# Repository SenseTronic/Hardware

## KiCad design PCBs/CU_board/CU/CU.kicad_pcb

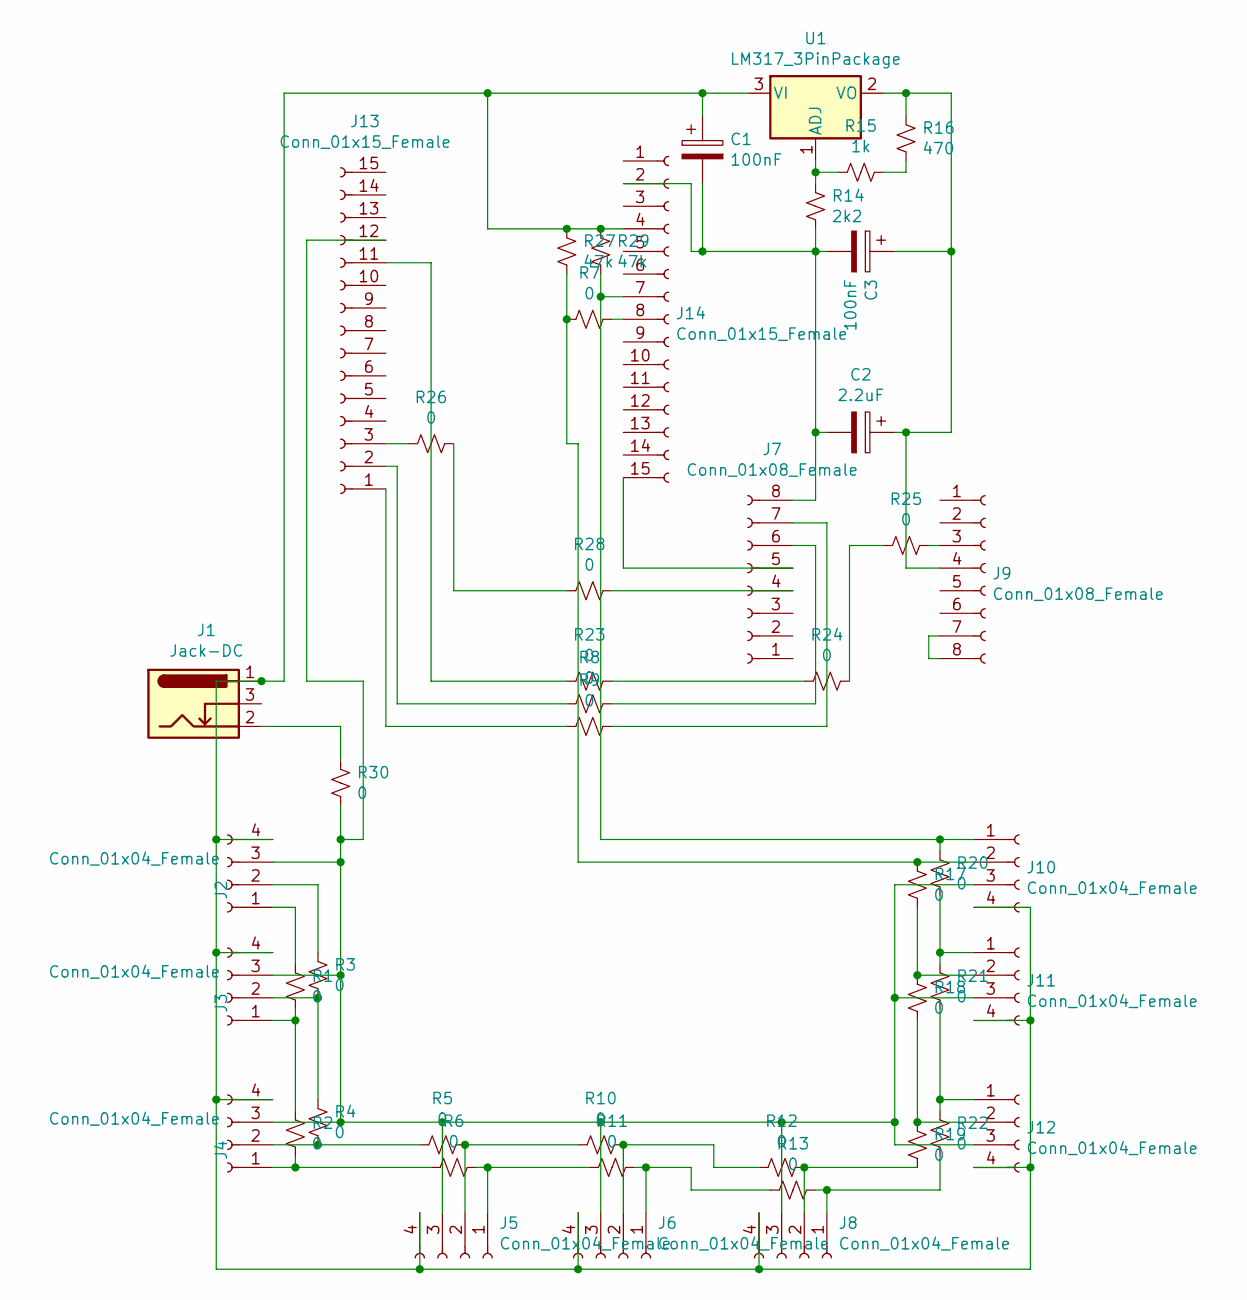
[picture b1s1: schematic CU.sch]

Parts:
C1, C3: 100nF; C_Disc_D4.3mm_W1.9mm_P5.00mm
C2: 2.2uF; CP_Radial_D5.0mm_P2.00mm
J1: Jack-DC; BarrelJack_Horizontal
J2, J3, J4, J5, J6, J8, J10, J11, J12: Conn_01x04_Female; PinSocket_1x04_P2.54mm_Vertical
J7, J9: Conn_01x08_Female; PinSocket_1x08_P2.54mm_Vertical
J13, J14: Conn_01x15_Female; PinSocket_1x15_P2.54mm_Vertical
R1, R2, R3, R4, R5, R6, R7, R8, R9, R10, R11, R12, R13, R17, R18, R19, R20, R21, R22, R23, R24, R25, R26, R28, R30: 0; R_Axial_DIN0207_L6.3mm_D2.5mm_P7.62mm_Horizontal
R14: 2k2; R_Axial_DIN0207_L6.3mm_D2.5mm_P7.62mm_Horizontal
R15: 1k; R_Axial_DIN0207_L6.3mm_D2.5mm_P2.54mm_Vertical
R16: 470; R_Axial_DIN0207_L6.3mm_D2.5mm_P2.54mm_Vertical
R27, R29: 47k; R_Axial_DIN0207_L6.3mm_D2.5mm_P7.62mm_Horizontal
U1: LM317_3PinPackage; TO-220-3_Vertical

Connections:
unnamed: C1.1, J1.1, J2.4, J3.4, J4.4, J5.4, J6.4, J8.4, J10.4, J11.4, J12.4, J14.4, R27.1, R29.1, U1.3 (VI)
unnamed: C1.2, C2.2, C3.2, J7.8, J14.2, R14.1
unnamed: C2.1, C3.1, J9.4, R16.1, U1.2 (VO)
unnamed: J1.2, R30.1
unnamed: J2.1, R1.1
unnamed: J2.2, R3.1
unnamed: J3.1, R1.2, R2.1
unnamed: J3.2, R3.2, R4.1
unnamed: J4.1, R2.2, R6.2
unnamed: J4.2, R4.2, R5.2
unnamed: J5.1, R6.1, R11.2
unnamed: J5.2, R5.1, R10.2
unnamed: J6.1, R11.1, R13.2
unnamed: J6.2, R10.1, R12.2
unnamed: J7.4, R28.1
unnamed: J7.6, R8.1
unnamed: J7.7, R9.1
unnamed: J8.1, R13.1, R22.1
unnamed: J8.2, R12.1, R19.1
unnamed: J9.3, R25.1
unnamed: J9.7, J9.8
unnamed: J10.1, J14.7, R20.2, R29.2
unnamed: J10.2, R7.2, R17.2, R27.2
unnamed: J2.3, J3.3, J4.3, J5.3, J6.3, J8.3, J10.3, J11.3, J12.3, J13.12, R30.2
unnamed: J11.1, R20.1, R21.2
unnamed: J11.2, R17.1, R18.2
unnamed: J12.1, R21.1, R22.2
unnamed: J12.2, R18.1, R19.2
unnamed: J13.1, R9.2
unnamed: J13.2, R8.2
unnamed: J13.3, R26.2
unnamed: J13.11, R23.2
unnamed: J14.8, R7.1
unnamed: J7.5, J14.15
unnamed: R14.2, R15.2, U1.1 (ADJ)
unnamed: R15.1, R16.2
unnamed: R23.1, R24.2
unnamed: R24.1, R25.2
unnamed: R26.1, R28.2

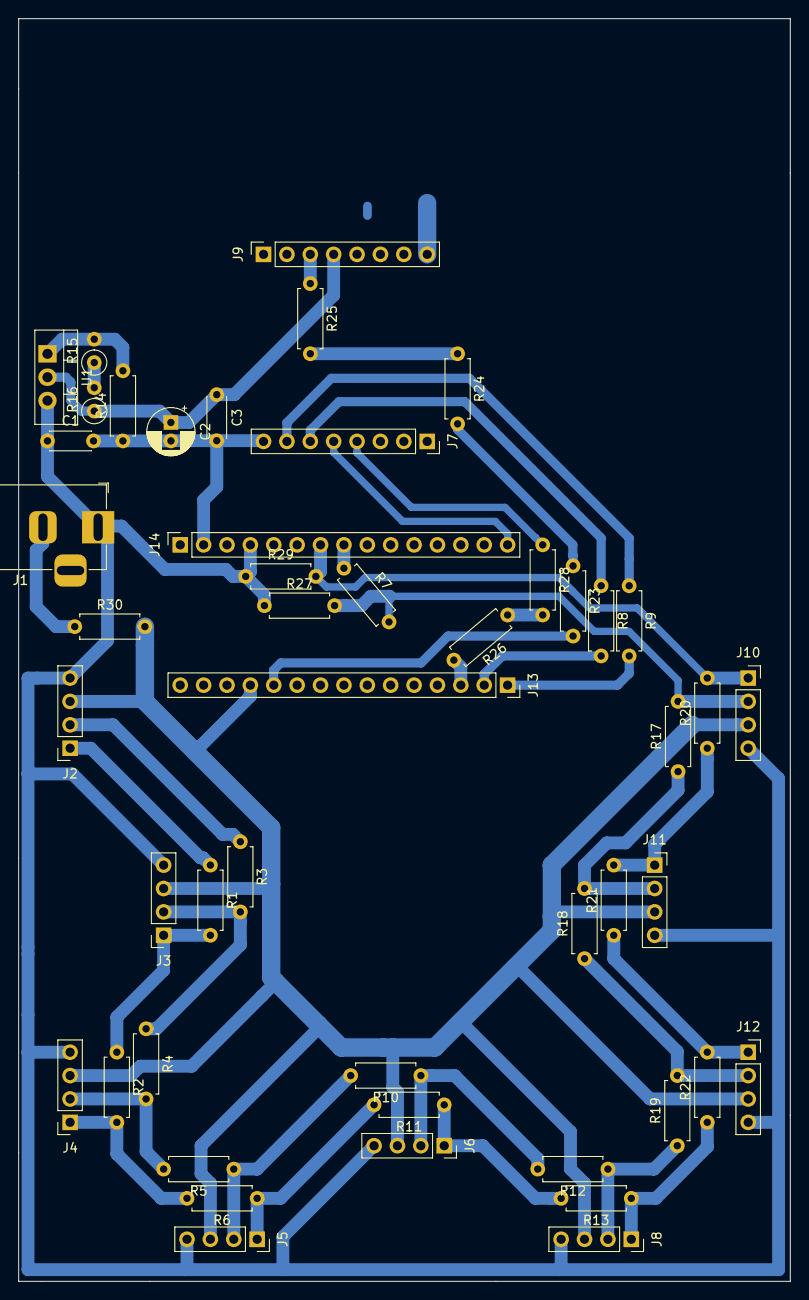
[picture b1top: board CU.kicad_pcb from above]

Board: 2 copper layers, 83.8 x 137.2 mm, 48 parts (0 on the bottom side), 39 nets.

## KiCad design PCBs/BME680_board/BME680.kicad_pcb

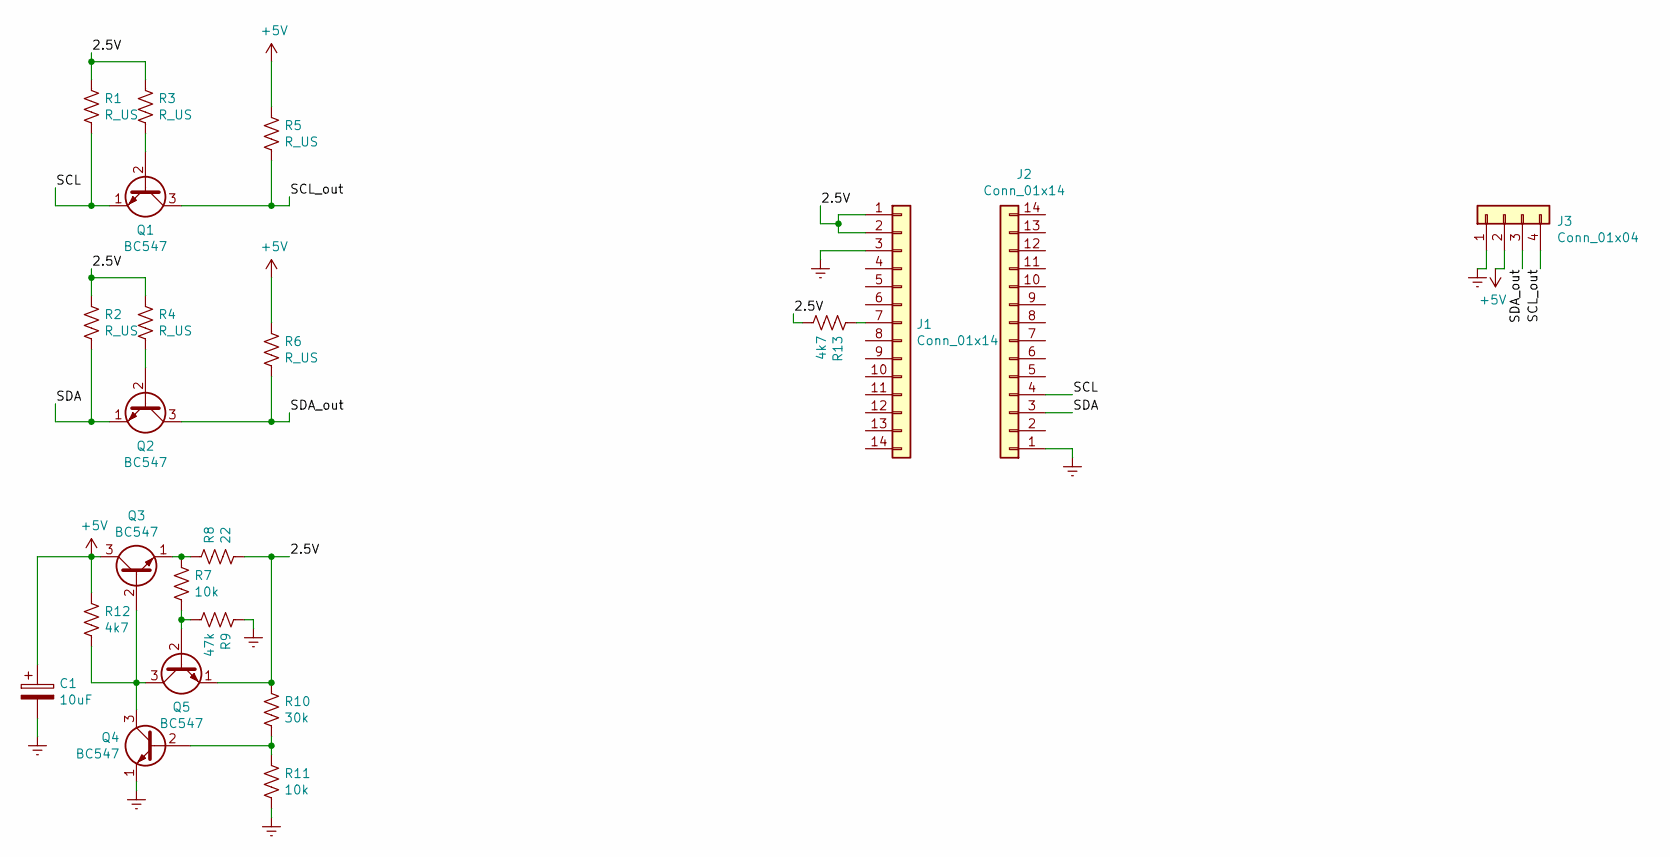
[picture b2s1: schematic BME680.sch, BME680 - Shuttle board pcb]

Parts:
C1: 10uF; CP_Radial_D5.0mm_P2.00mm
J1, J2: Conn_01x14; PinSocket_1x14_P2.54mm_Vertical
J3: Conn_01x04; PinHeader_1x04_P2.54mm_Horizontal
Q1, Q2, Q3, Q4, Q5: BC547; TO-92_Inline
R1, R2, R3, R4, R5, R6: R_US; R_Axial_DIN0207_L6.3mm_D2.5mm_P2.54mm_Vertical
R7, R11: 10k; R_Axial_DIN0207_L6.3mm_D2.5mm_P5.08mm_Vertical
R8: 22; R_Axial_DIN0207_L6.3mm_D2.5mm_P5.08mm_Vertical
R9: 47k; R_Axial_DIN0207_L6.3mm_D2.5mm_P5.08mm_Vertical
R10: 30k; R_Axial_DIN0207_L6.3mm_D2.5mm_P5.08mm_Vertical
R12: 4k7; R_Axial_DIN0207_L6.3mm_D2.5mm_P5.08mm_Vertical
R13: 4k7; R_Axial_DIN0207_L6.3mm_D2.5mm_P7.62mm_Horizontal

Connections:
+5V: C1.1, J3.2, Q3.3 (C), R5.1, R6.1, R12.1
/2.5V: J1.1, J1.2, Q5.1 (E), R1.1, R2.1, R3.1, R4.1, R8.2, R10.1, R13.2
/SCL: J2.4, Q1.1 (E), R1.2
/SCL_out: J3.4, Q1.3 (C), R5.2
/SDA: J2.3, Q2.1 (E), R2.2
/SDA_out: J3.3, Q2.3 (C), R6.2
Earth: C1.2, J1.3, J2.1, J3.1, Q4.1 (E), R9.1, R11.2
unnamed: J1.7, R13.1
unnamed: Q1.2 (B), R3.2
unnamed: Q2.2 (B), R4.2
unnamed: Q3.1 (E), R7.1, R8.1
unnamed: Q3.2 (B), Q4.3 (C), Q5.3 (C), R12.2
unnamed: Q4.2 (B), R10.2, R11.1
unnamed: Q5.2 (B), R7.2, R9.2

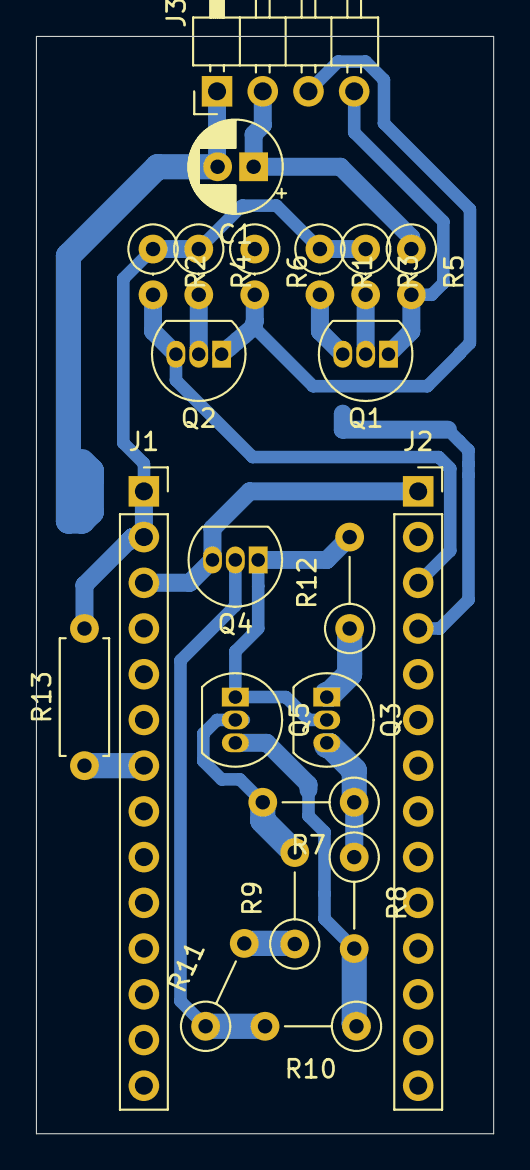
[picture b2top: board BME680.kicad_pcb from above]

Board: 2 copper layers, 25.4 x 61.0 mm, 22 parts (0 on the bottom side), 14 nets.

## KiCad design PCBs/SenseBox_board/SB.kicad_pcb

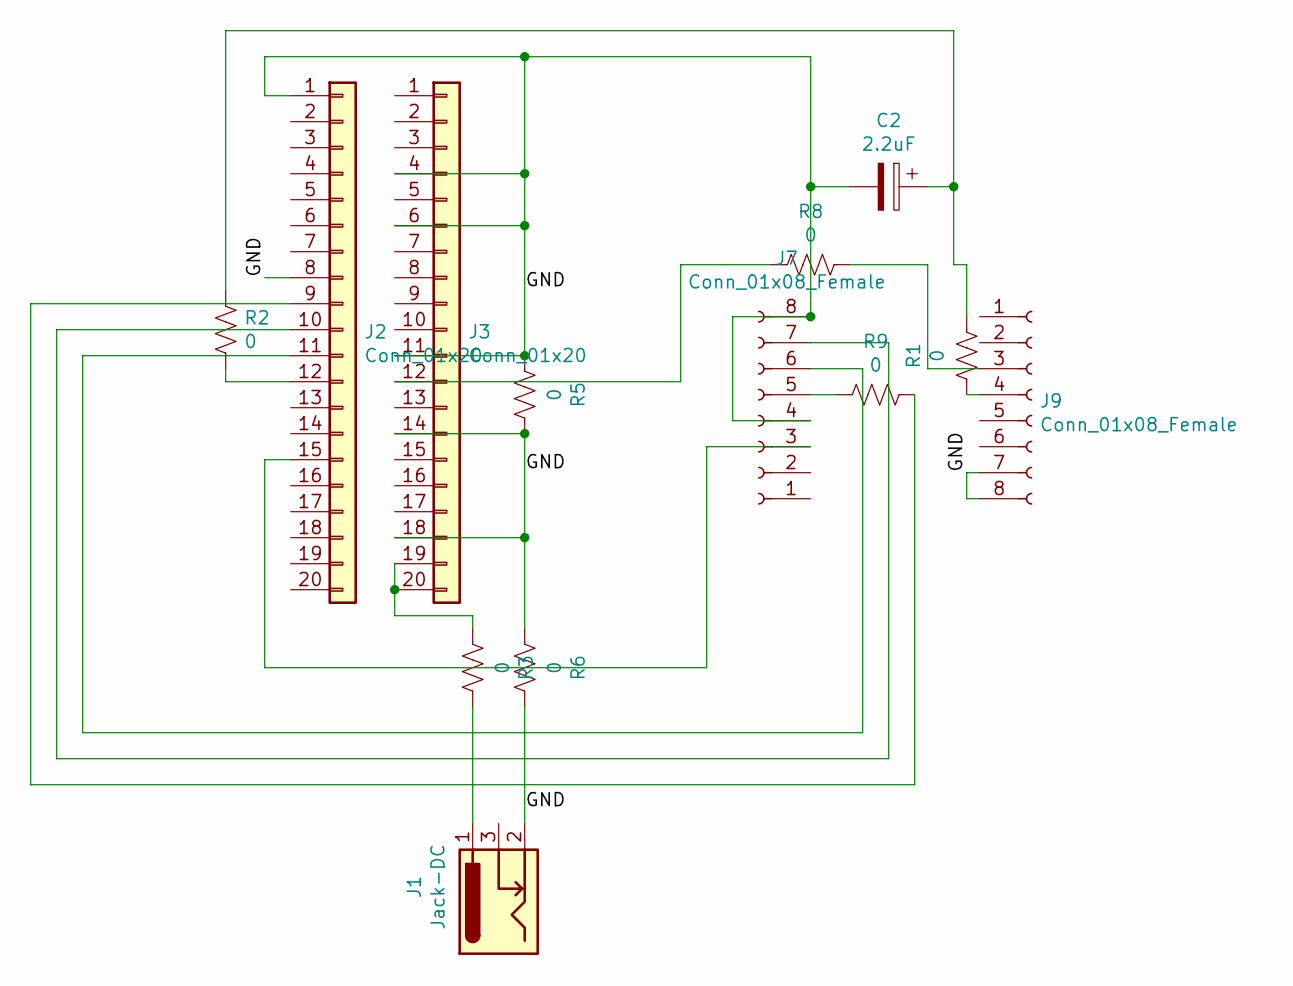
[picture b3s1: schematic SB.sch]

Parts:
C2: 2.2uF; CP_Radial_D5.0mm_P2.00mm
J1: Jack-DC; BarrelJack_Horizontal
J2, J3: Conn_01x20; PinSocket_1x20_P2.54mm_Vertical
J7, J9: Conn_01x08_Female; PinSocket_1x08_P2.54mm_Vertical
R1, R5, R8, R9: 0; R_Axial_DIN0207_L6.3mm_D2.5mm_P7.62mm_Horizontal
R2: 0; R_Axial_DIN0207_L6.3mm_D2.5mm_P15.24mm_Horizontal
R3, R6: 0; R_Axial_DIN0207_L6.3mm_D2.5mm_P10.16mm_Horizontal

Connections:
/GND: C2.2, J1.2, J2.1, J2.8, J3.4, J3.6, J3.11, J3.14, J3.18, J7.4, J7.8, J9.7, J9.8, R5.1, R5.2, R6.1, R6.2
unnamed: C2.1, R1.1, R2.2
unnamed: J1.1, R3.1
unnamed: J2.9, R9.1
unnamed: J2.10, J7.7
unnamed: J2.11, J7.6
unnamed: J2.12, R2.1
unnamed: J2.15, J7.3
unnamed: J3.12, R8.2
unnamed: J3.19, J3.20, R3.2
unnamed: J7.5, R9.2
unnamed: J9.3, R8.1
unnamed: J9.4, R1.2

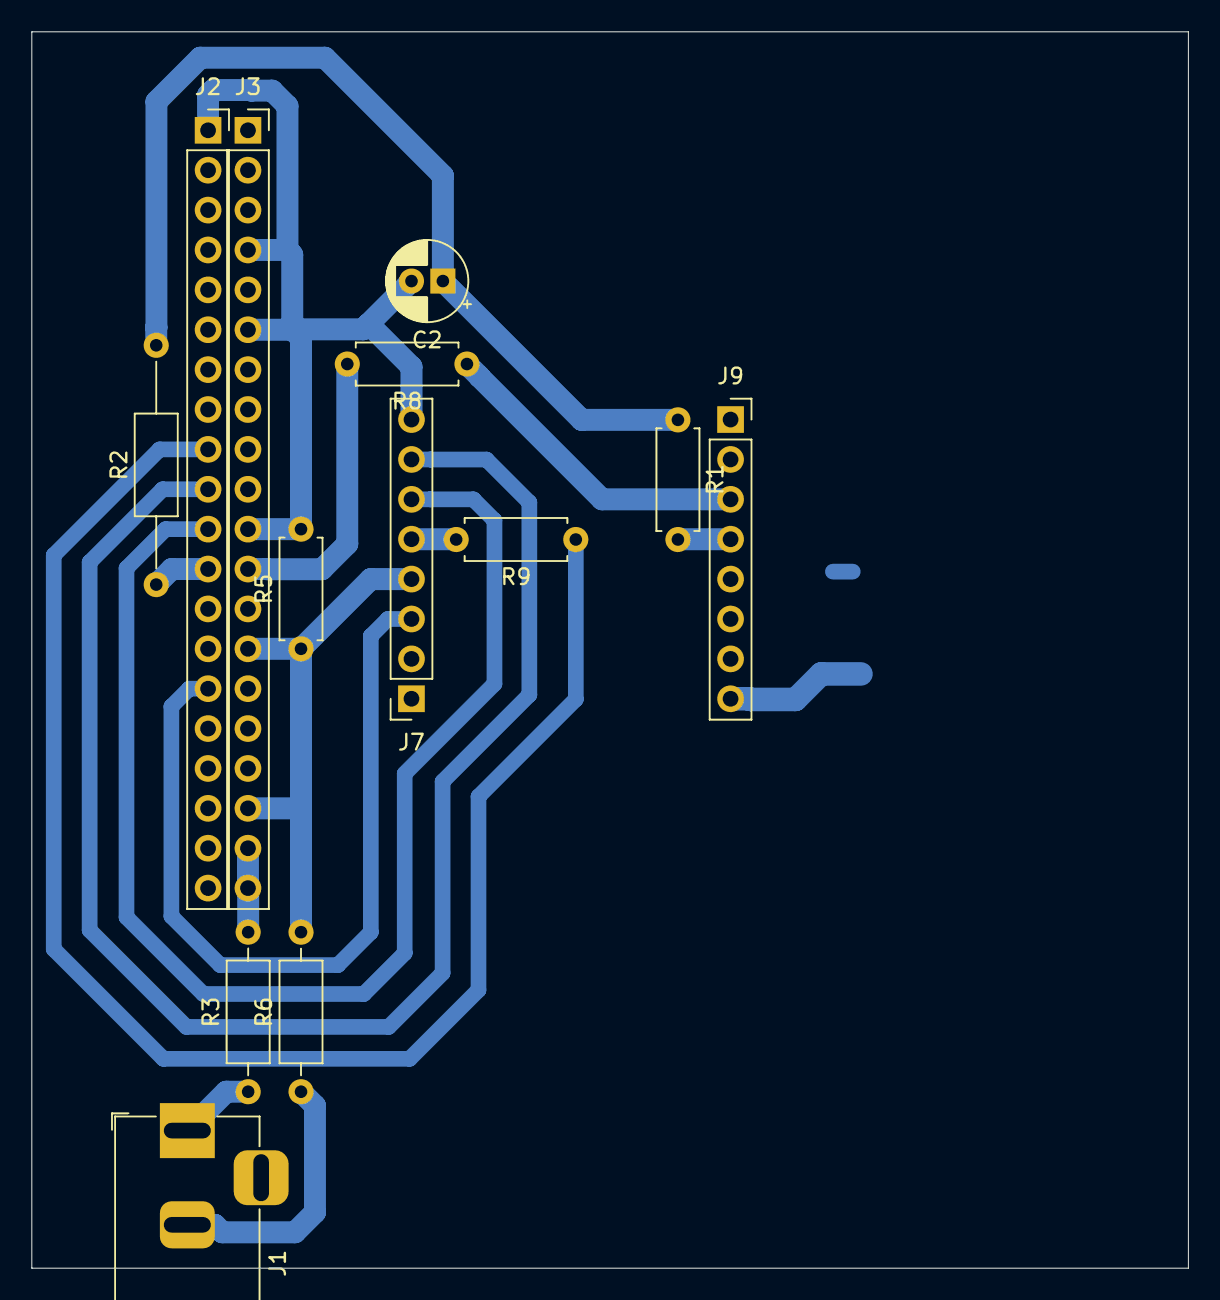
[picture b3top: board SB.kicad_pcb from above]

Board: 2 copper layers, 73.7 x 78.7 mm, 13 parts (0 on the bottom side), 13 nets.

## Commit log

2020-01-26 Sensors_Tests
2020-01-26 Uma alteração para testar
2020-01-27 testing permissions
2020-01-27 removed useless teste.txt file
2020-03-15 Add CO conversion stuff
2020-03-27 Added Nano as attiny85 programmer PCB
2020-03-27 Added MQ9 PCB
2020-04-01 Added SCD30 PCB
2020-04-19 Codigo para calibração do MQ9 e conversão para ppms
2020-04-28 added bme680 pcb, still needs testing
2020-04-28 added bme680 pcb simulations
2020-05-16 added CU board
2020-05-16 organization of CU board folder
2020-05-20 added TSL2561 board
2020-05-20 added sensebox board
2020-06-04 added gerbers
